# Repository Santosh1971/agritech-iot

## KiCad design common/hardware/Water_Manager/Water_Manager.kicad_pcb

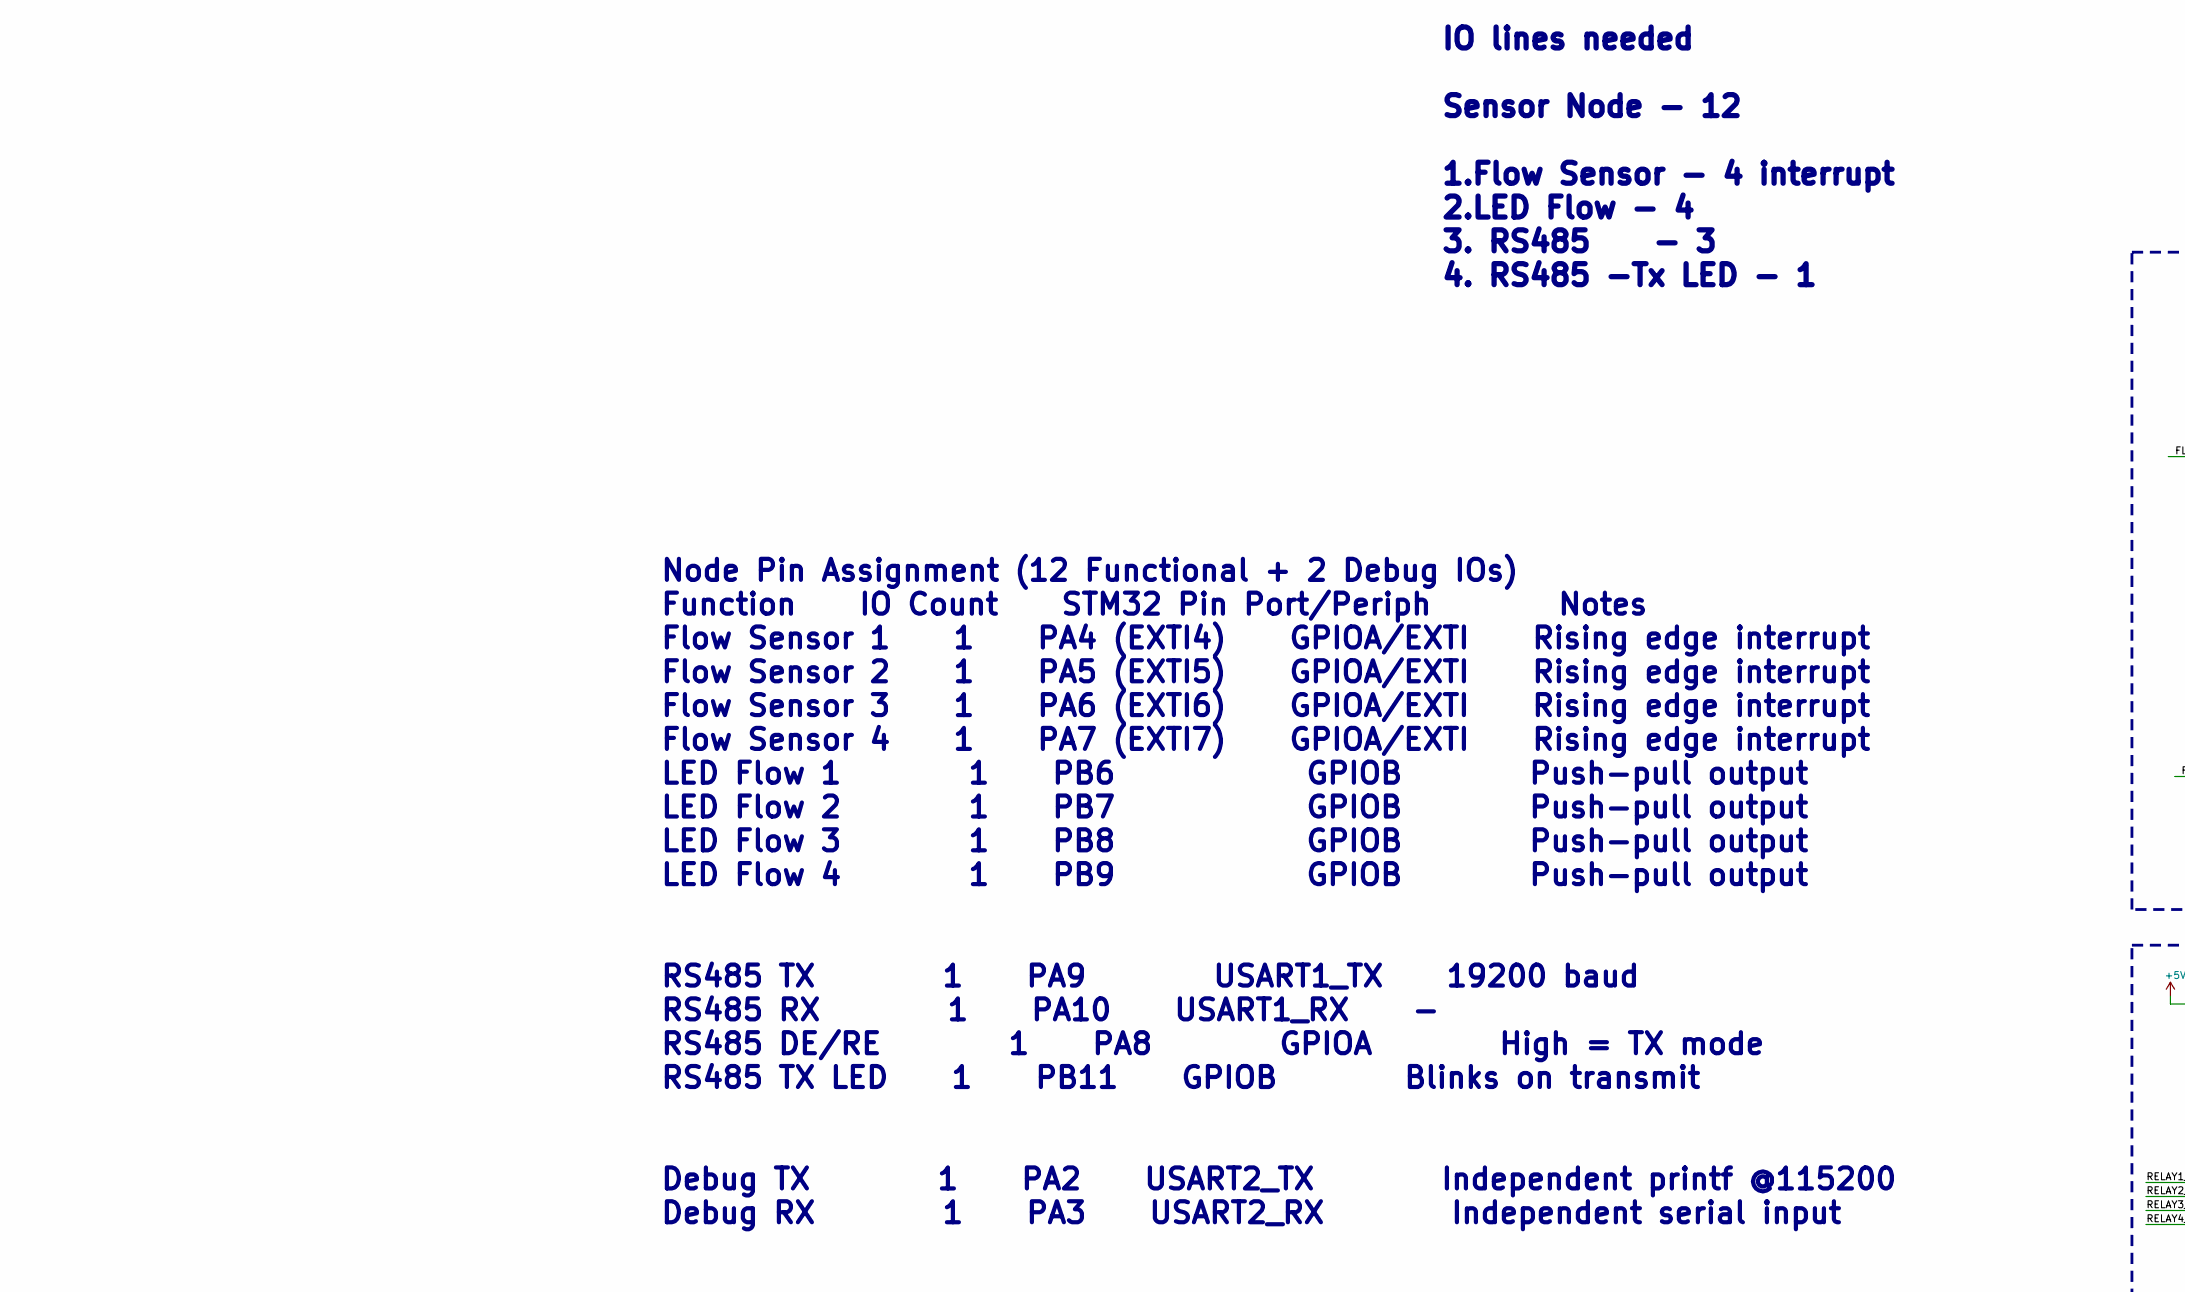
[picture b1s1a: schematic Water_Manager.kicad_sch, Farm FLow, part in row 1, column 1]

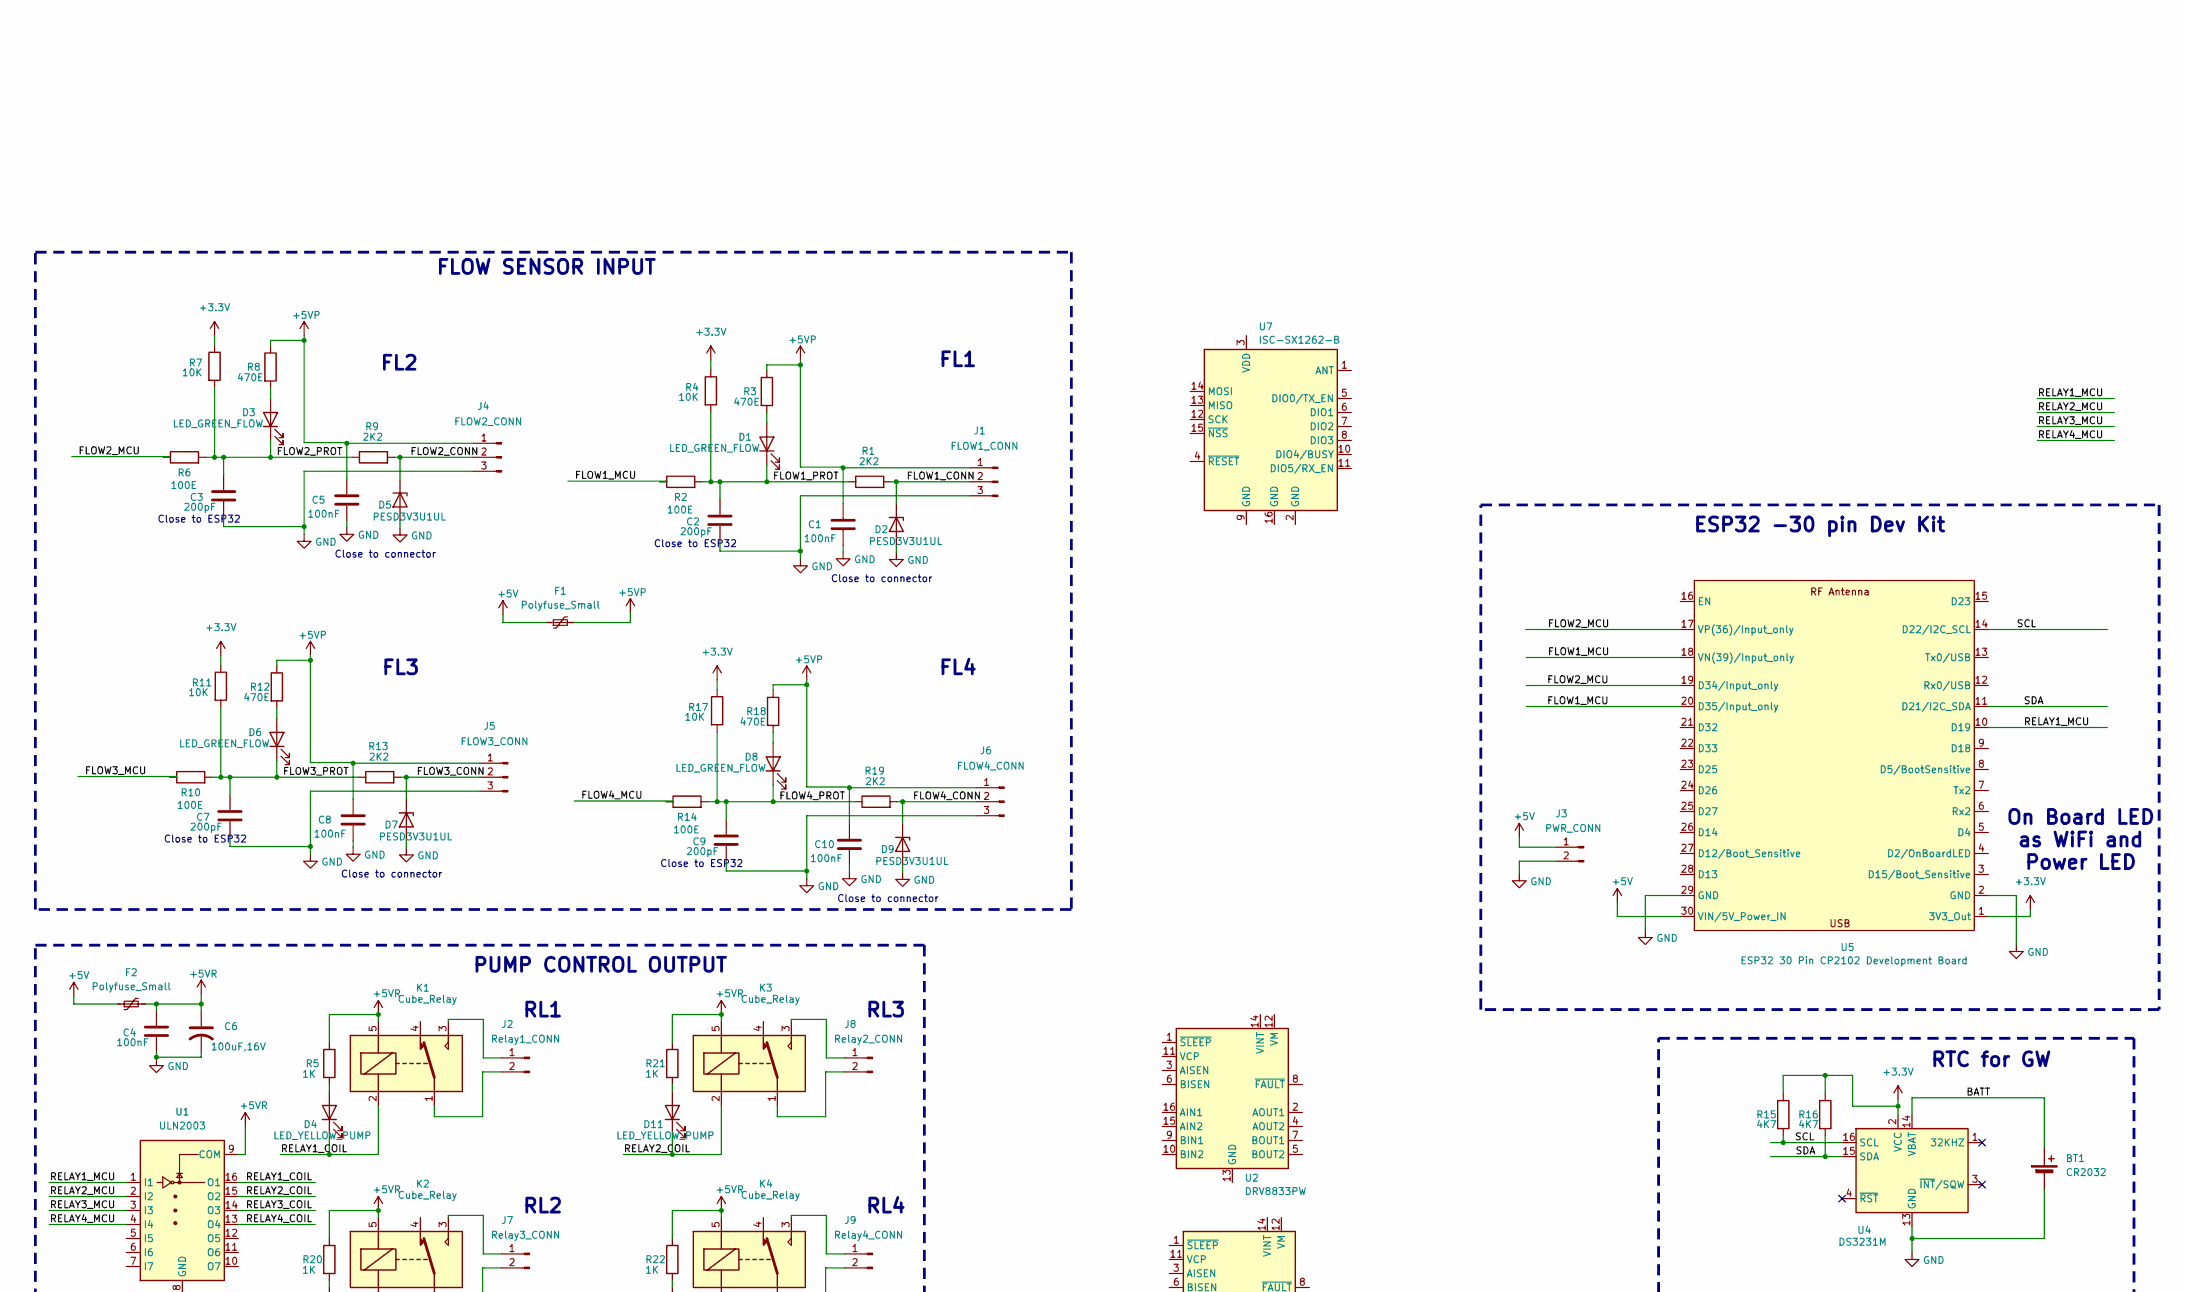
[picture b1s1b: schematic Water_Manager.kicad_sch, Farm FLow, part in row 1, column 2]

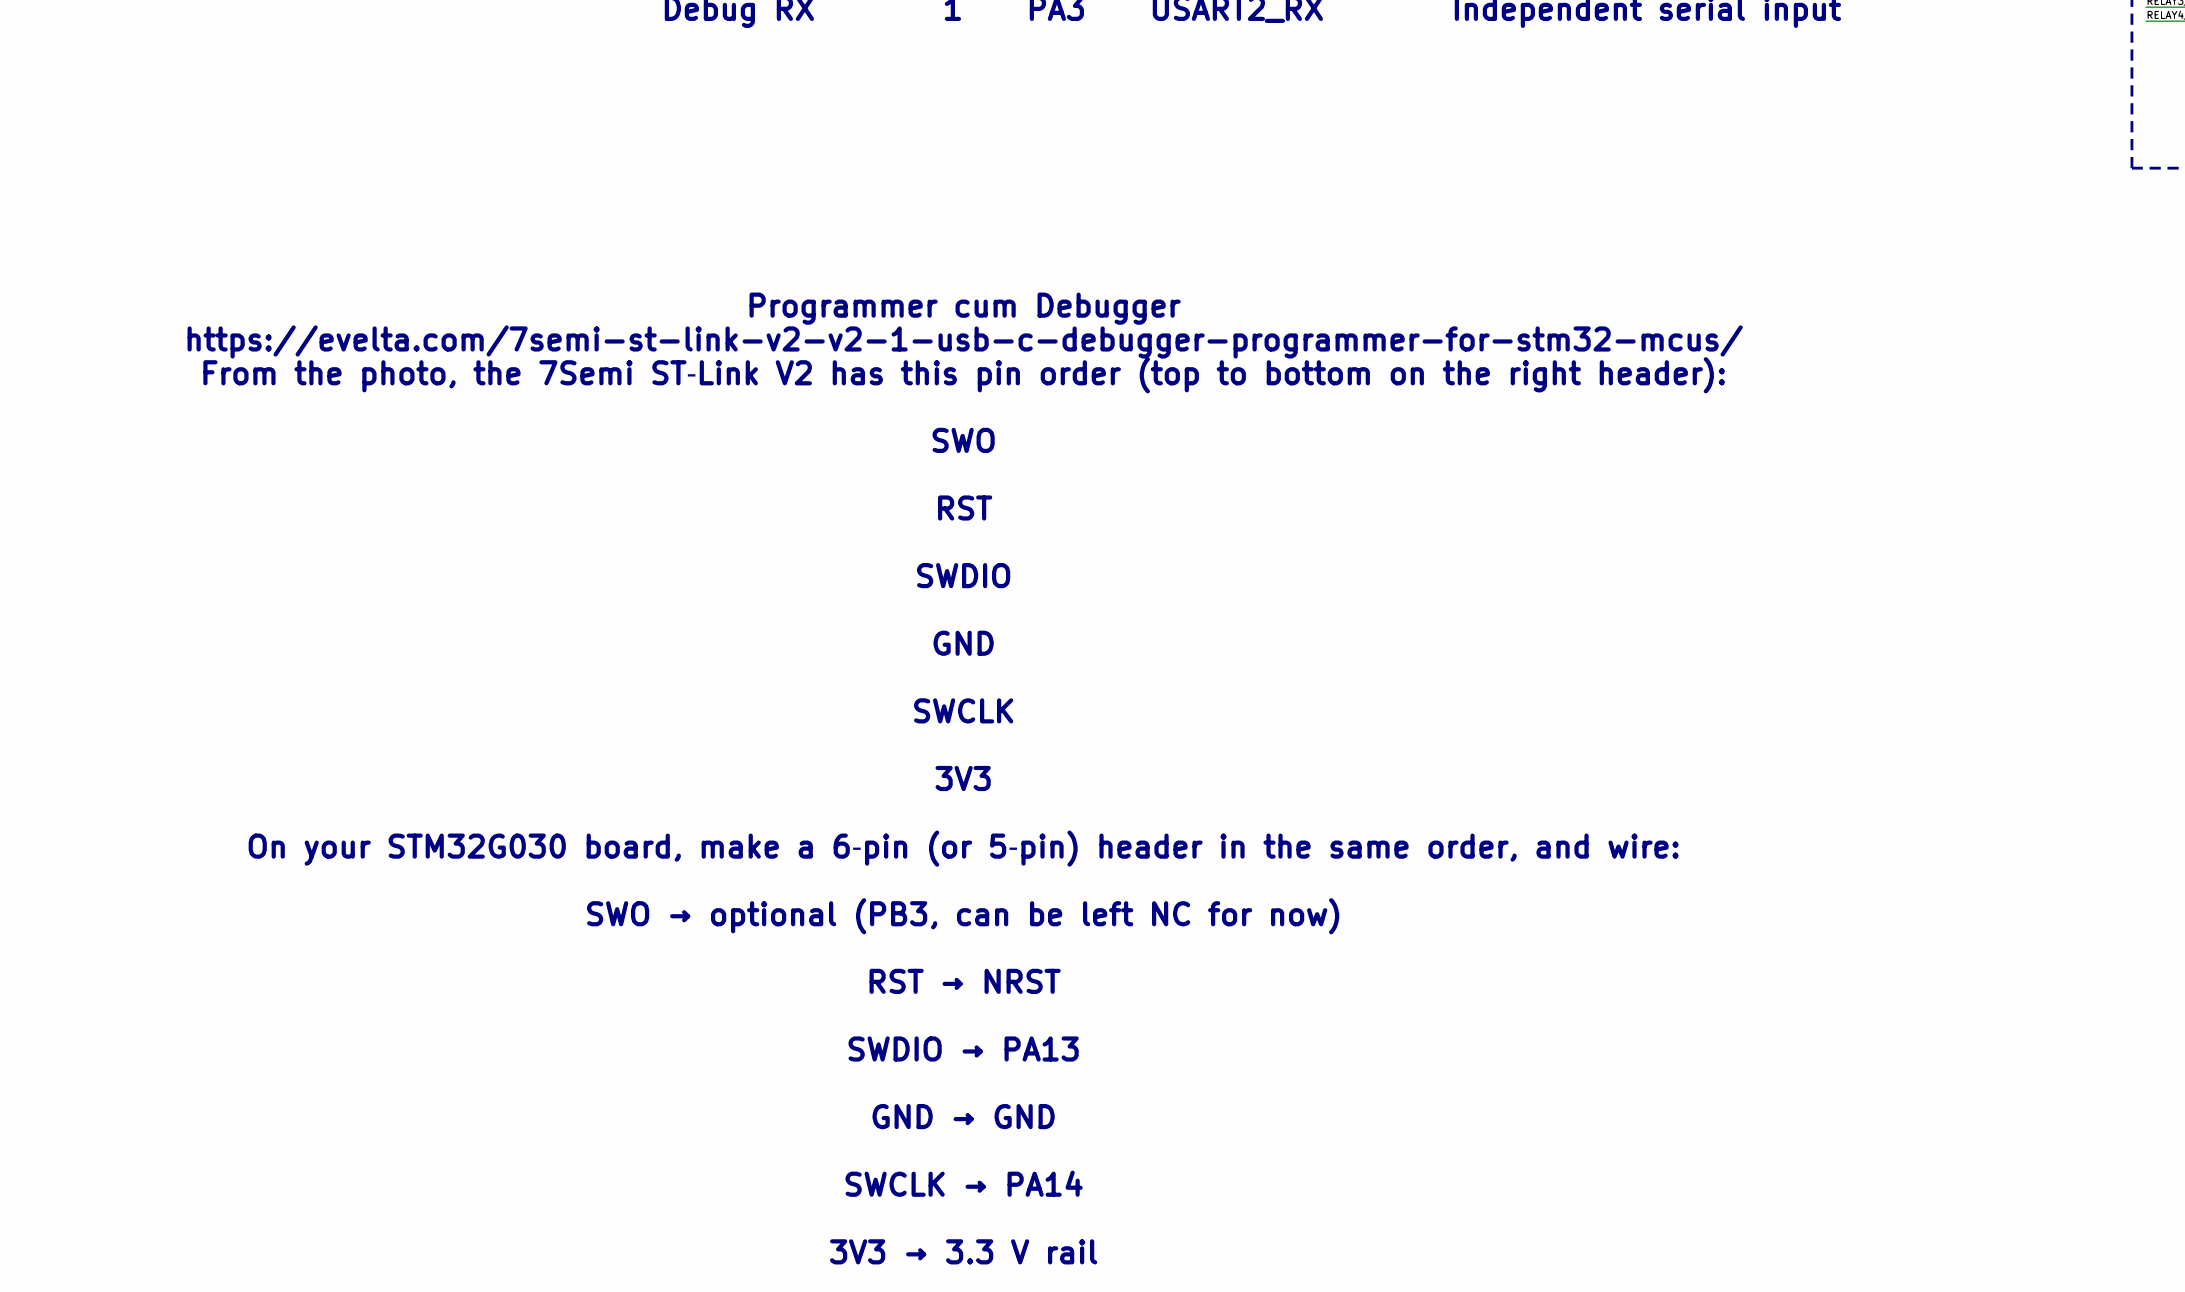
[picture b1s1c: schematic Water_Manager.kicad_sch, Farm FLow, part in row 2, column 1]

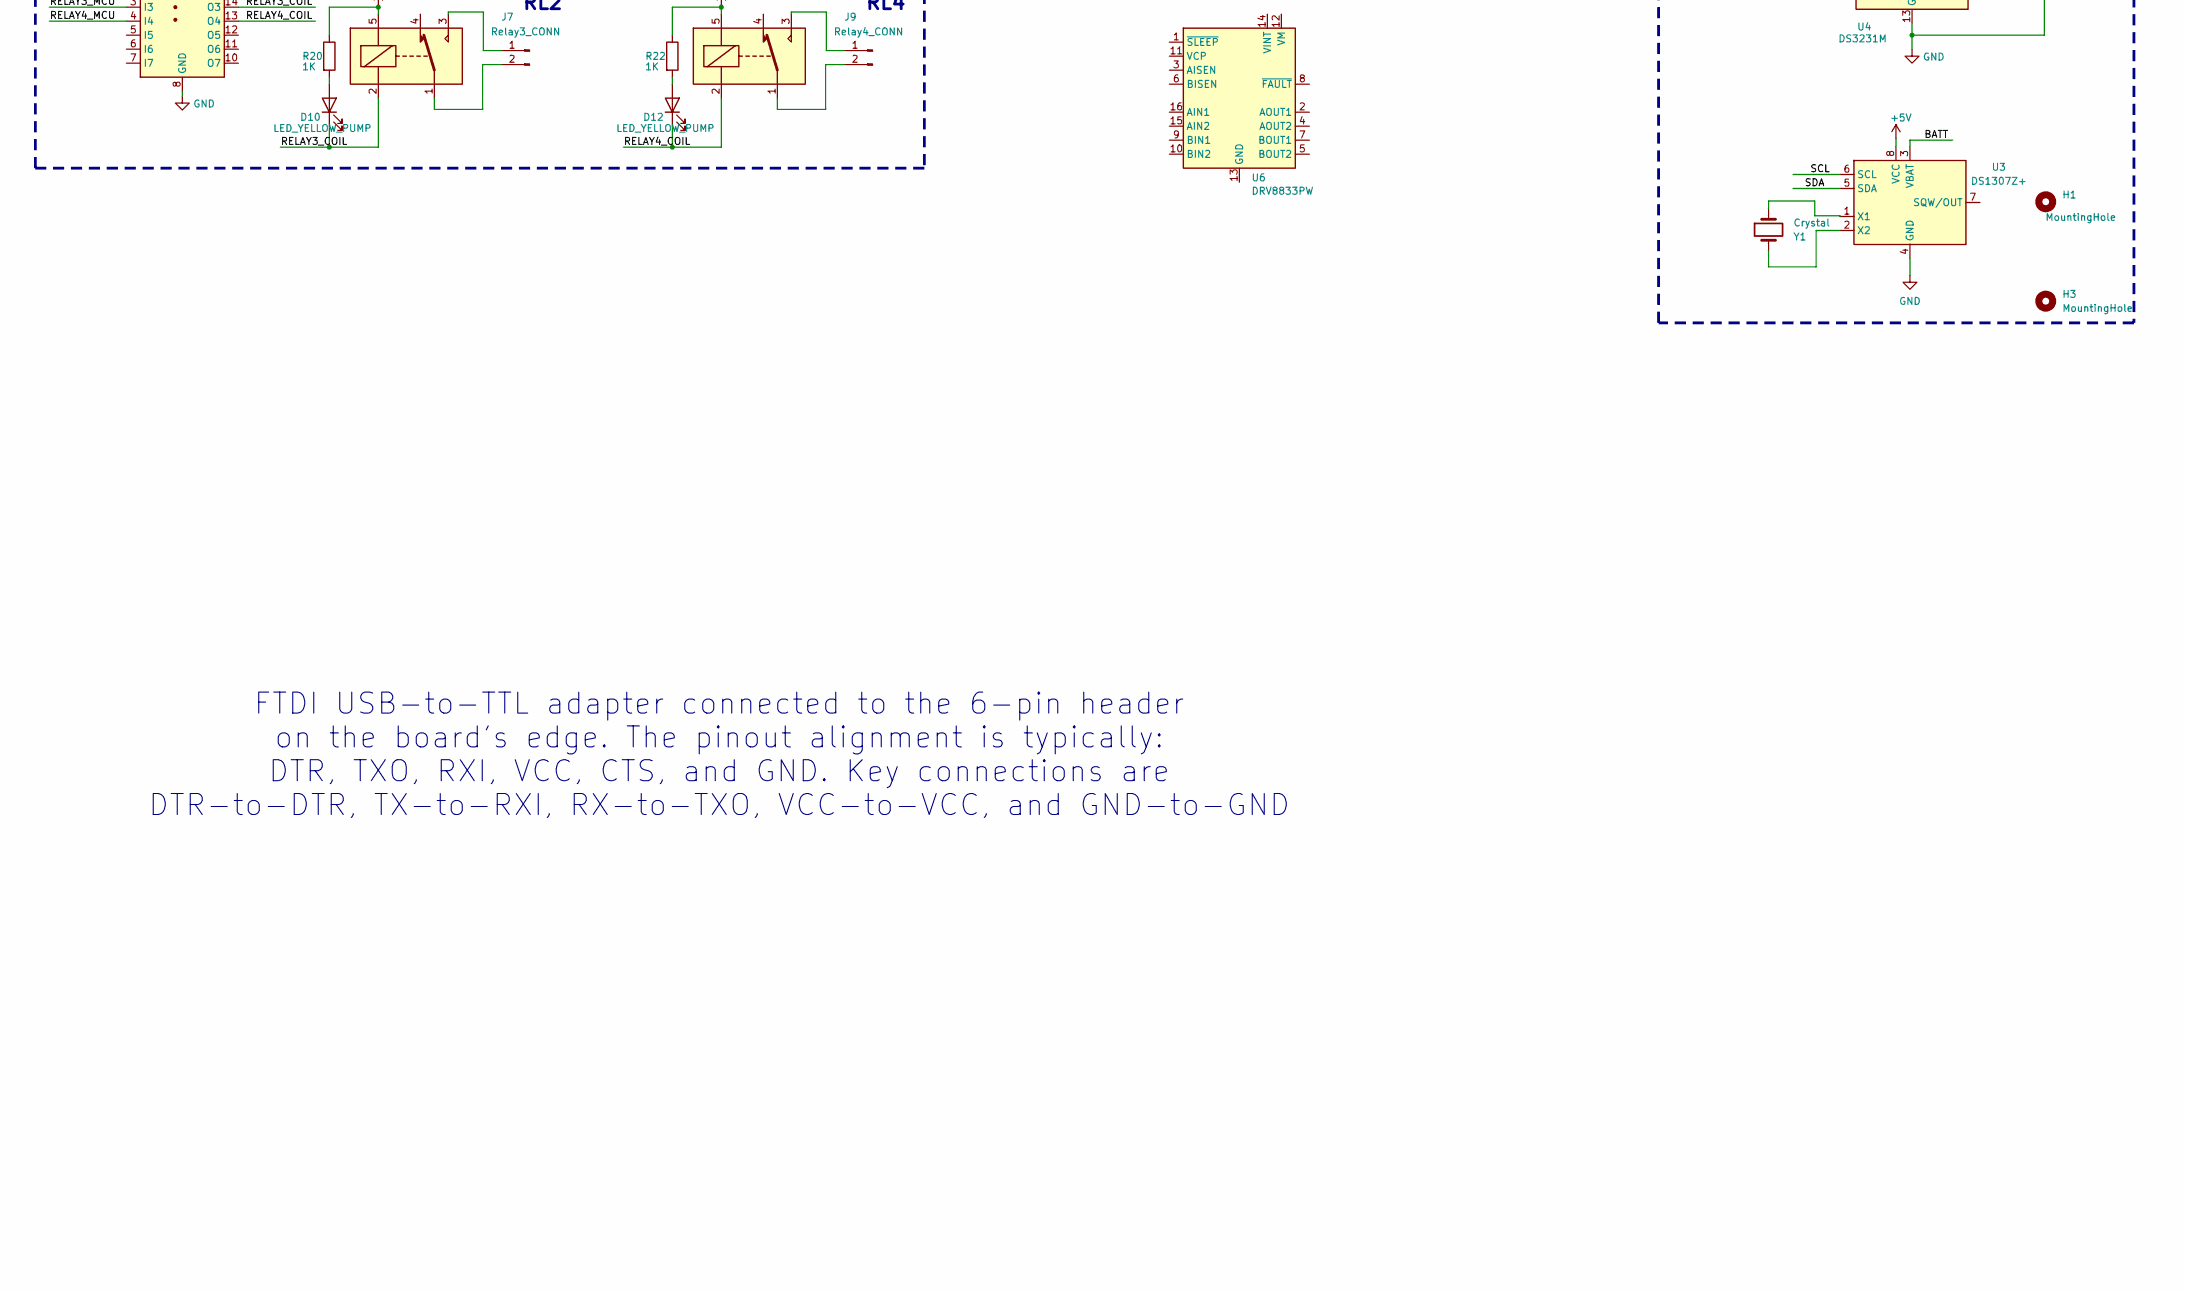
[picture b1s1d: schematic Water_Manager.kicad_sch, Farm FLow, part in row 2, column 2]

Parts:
BT1: CR2032
C1, C4, C5, C8, C10: 100nF; C_0805_2012Metric
C2, C3, C7, C9: 200pF; C_0805_2012Metric
C6: 100uF,16V; C_Radial_D5.0mm_H7.0mm_P2.00mm
D1, D3, D6, D8: LED_GREEN_FLOW; LED_0603_1608Metric
D2, D5, D7, D9: PESD3V3U1UL; D_SOD-882
D4, D10, D11, D12: LED_YELLOW_PUMP; LED_0603_1608Metric
F1, F2: Polyfuse_Small; L_1206_3216Metric
H1, H3: MountingHole; MountingHole_3.2mm_M3
J1: FLOW1_CONN; JST_EH_B3B-EH-A_1x03_P2.50mm_Vertical
J2: Relay1_CONN; JST_EH_B2B-EH-A_1x02_P2.50mm_Vertical
J3: PWR_CONN
J4: FLOW2_CONN; JST_EH_B3B-EH-A_1x03_P2.50mm_Vertical
J5: FLOW3_CONN; JST_EH_B3B-EH-A_1x03_P2.50mm_Vertical
J6: FLOW4_CONN; JST_EH_B3B-EH-A_1x03_P2.50mm_Vertical
J7: Relay3_CONN; JST_EH_B2B-EH-A_1x02_P2.50mm_Vertical
J8: Relay2_CONN; JST_EH_B2B-EH-A_1x02_P2.50mm_Vertical
J9: Relay4_CONN; JST_EH_B2B-EH-A_1x02_P2.50mm_Vertical
K1, K2, K3, K4: Cube_Relay; Relay_SPDT_SANYOU_SRD_Series_Form_C
R1, R9, R13, R19: 2K2; R_0805_2012Metric
R2, R6, R10, R14: 100E; R_0805_2012Metric
R3, R8, R12, R18: 470E; R_0805_2012Metric
R4, R7, R11, R17: 10K; R_0805_2012Metric
R5, R20, R21, R22: 1K; R_0805_2012Metric
R15, R16: 4K7; R_0805_2012Metric
U1: ULN2003; SOIC-16W_5.3x10.2mm_P1.27mm
U2, U6: DRV8833PW; TSSOP-16_4.4x5mm_P0.65mm
U3: DS1307Z+; SOIC-8_3.9x4.9mm_P1.27mm
U4: DS3231M; SOIC-16W_7.5x10.3mm_P1.27mm
U5: ESP32 30 Pin CP2102 Development Board; ESP32-C3-DevKitM-1
U7: ISC-SX1262-B; ISC-LoRa
Y1: Crystal; Crystal_AT310_D3.0mm_L10.0mm_Horizontal

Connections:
+3.3V: R4.1, R7.1, R11.1, R15.1, R16.1, R17.1, U4.2 (VCC), U5.1 (3V3_Out)
+5V: F1.1, F2.1, J3.1, U3.8 (VCC), U5.30 (VIN/5V_Power_IN); also elsewhere on the board
+5VP: C1.1, C5.1, C8.1, C10.1, F1.2, J1.1, J4.1, J5.1, J6.1, R3.1, R8.1, R12.1, R18.1
+5VR: C4.1, C6.1, F2.2, K1.5, K2.5, K3.5, K4.5, R5.1, R20.1, R21.1, R22.1, U1.9 (COM)
/BATT: BT1.1 (+), U3.3 (VBAT), U4.14 (VBAT)
/FLOW1_CONN: D2.1 (K), J1.2, R1.2
/FLOW1_MCU: R2.1, U5.18 (VN(39)/Input_only), U5.20 (D35/Input_only)
/FLOW1_PROT: C2.1, D1.1 (K), R1.1, R2.2, R4.2
/FLOW2_CONN: D5.1 (K), J4.2, R9.2
/FLOW2_MCU: R6.1, U5.17 (VP(36)/Input_only), U5.19 (D34/Input_only)
/FLOW2_PROT: C3.1, D3.1 (K), R6.2, R7.2, R9.1
/FLOW3_CONN: D7.1 (K), J5.2, R13.2
/FLOW3_MCU: R10.1
/FLOW3_PROT: C7.1, D6.1 (K), R10.2, R11.2, R13.1
/FLOW4_CONN: D9.1 (K), J6.2, R19.2
/FLOW4_MCU: R14.1
/FLOW4_PROT: C9.1, D8.1 (K), R14.2, R17.2, R19.1
/RELAY1_COIL: D4.1 (K), K1.2, U1.16 (O1)
/RELAY1_MCU: U1.1 (I1), U5.10 (D19)
/RELAY2_COIL: D11.1 (K), K3.2, U1.15 (O2)
/RELAY2_MCU: U1.2 (I2)
/RELAY3_COIL: D10.1 (K), K2.2, U1.14 (O3)
/RELAY3_MCU: U1.3 (I3)
/RELAY4_COIL: D12.1 (K), K4.2, U1.13 (O4)
/RELAY4_MCU: U1.4 (I4)
/SCL: R15.2, U3.6 (SCL), U4.16 (SCL), U5.14 (D22/I2C_SCL)
/SDA: R16.2, U3.5 (SDA), U4.15 (SDA), U5.11 (D21/I2C_SDA)
GND: BT1.2 (-), C1.2, C2.2, C3.2, C4.2, C5.2, C6.2, C7.2, C8.2, C9.2, C10.2, D2.2 (A), D5.2 (A), D7.2 (A), D9.2 (A), J1.3, J3.2, J4.3, J5.3, J6.3, U1.8 (GND), U3.4 (GND), U4.5 (GND), U4.6 (GND), U4.7 (GND), U4.8 (GND), U4.9 (GND), U4.10 (GND), U4.11 (GND), U4.12 (GND), U4.13 (GND), U5.2 (GND), U5.29 (GND); also elsewhere on the board
unnamed: D1.2 (A), R3.2
unnamed: D3.2 (A), R8.2
unnamed: D4.2 (A), R5.2
unnamed: D6.2 (A), R12.2
unnamed: D8.2 (A), R18.2
unnamed: D10.2 (A), R20.2
unnamed: D11.2 (A), R21.2
unnamed: D12.2 (A), R22.2
unnamed: J2.1, K1.3
unnamed: J2.2, K1.1
unnamed: J7.1, K2.3
unnamed: J7.2, K2.1
unnamed: J8.1, K3.3
unnamed: J8.2, K3.1
unnamed: J9.1, K4.3
unnamed: J9.2, K4.1
unnamed: U3.1 (X1), Y1.1
unnamed: U3.2 (X2), Y1.2
unnamed: U7.2 (GND), U7.9 (GND), U7.16 (GND)

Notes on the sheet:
Close to connector
Close to ESP32
FL4
Programmer cum Debugger https://evelta.com/7semi-st-link-v2-v2-1-usb-c-debugger-programmer-for-stm32-mcus/ From the photo, the 7Semi ST‑Link V2 has this pin order (top to bottom on the right header): SWO RST SWDIO GND SWCLK 3V3 On your STM32G030 board, make a 6‑pin (or 5‑pin) header in the same ord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
RL3
IO lines needed Sensor Node - 12 1.Flow Sensor - 4 interrupt 2.LED Flow - 4 3. RS485 - 3 4. RS485 -Tx LED - 1
RTC for GW
RL4
On Board LED as WiFi and Power LED
Node Pin Assignment (12 Functional + 2 Debug IOs) Function IO Count STM32 Pin Port/Periph Notes Flow Sensor 1 1 PA4 (EXTI4) GPIOA/EXTI Rising edge interrupt Flow Sensor 2 1 PA5 (EXTI5) GPIOA/EXTI Rising edge interrupt Flow Sensor 3 1 PA6 (EXTI6) GPIOA/EXTI Rising edge interrupt Flow Sensor 4 1 PA7 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
FTDI USB-to-TTL adapter connected to the 6-pin header on the board's edge. The pinout alignment is typically: DTR, TXO, RXI, VCC, CTS, and GND. Key connections are DTR-to-DTR, TX-to-RXI, RX-to-TXO, VCC-to-VCC, and GND-to-GND
PUMP CONTROL OUTPUT
ESP32 -30 pin Dev Kit
RL1
FL3
RL2
FL1
FLOW SENSOR INPUT
FL2

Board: 2 copper layers, 76 parts (45 on the bottom side), 42 nets, no tracks yet.

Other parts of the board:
.: MountingHole; MountingHole_3.2mm_M3
J3#2: PWR_CONN; PinHeader_1x02_P2.00mm_Vertical
J3#3, J3#4, J3#5, J3#6: PWR_CONN; JST_EH_B2B-EH-A_1x02_P2.50mm_Vertical

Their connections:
+5V: J3#2.1, J3#4.1; also elsewhere on the board
GND: J3#2.2, J3#4.2; also elsewhere on the board

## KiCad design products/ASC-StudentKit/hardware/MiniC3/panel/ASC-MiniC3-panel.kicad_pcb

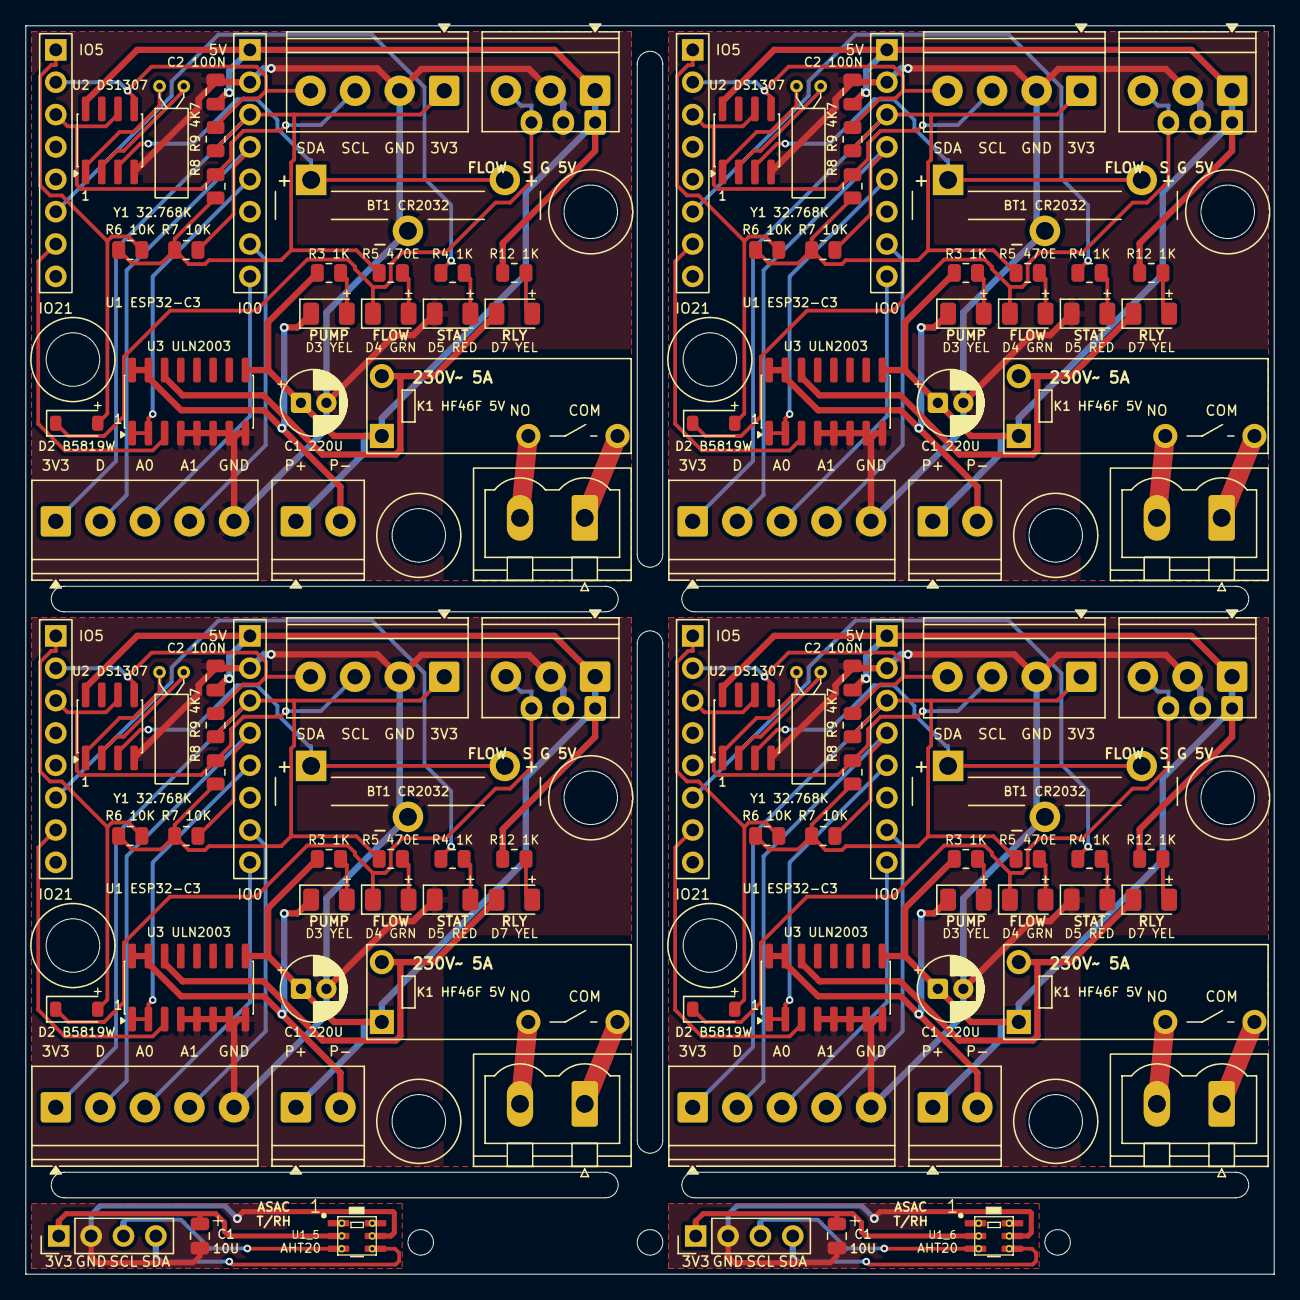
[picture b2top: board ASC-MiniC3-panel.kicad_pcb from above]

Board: 2 copper layers, 98.0 x 98.0 mm, 122 parts (0 on the bottom side), 104 nets.

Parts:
BT1_1, BT1_2, BT1_3, BT1_4: CR2032 tabbed; Battery_CR2032_Vertical_3pin
C1_1, C1_2, C1_3, C1_4: 220u 10V; CP_Radial_D5.0mm_P2.00mm
C1_5, C1_6: 10u; C_0805_2012Metric
C2_1, C2_2, C2_3, C2_4: 100n; C_0805_2012Metric
D2_1, D2_2, D2_3, D2_4: B5819W; D_SOD-123
D3_1, D3_2, D3_3, D3_4: PUMP yellow; LED_1206_3216Metric
D4_1, D4_2, D4_3, D4_4: FLOW yellow-green; LED_1206_3216Metric
D5_1, D5_2, D5_3, D5_4: STATUS red; LED_1206_3216Metric
D7_1, D7_2, D7_3, D7_4: RELAY yellow; LED_1206_3216Metric
H1_1, H1_2, H1_3, H1_4, H2_1, H2_2, H2_3, H2_4, H3_1, H3_2, H3_3, H3_4: SNAP 4.2; Snap_Standoff_4.2mm
J1_1, J1_2, J1_3, J1_4: PUMP; TerminalBlock_Phoenix_PT-1,5-2-3.5-H_1x02_P3.50mm_Horizontal
J1_5, J1_6: CABLE; PinHeader_1x04_P2.54mm_Vertical
J3_1, J3_2, J3_3, J3_4: AUX; TerminalBlock_Phoenix_PT-1,5-5-3.5-H_1x05_P3.50mm_Horizontal
J4_1, J4_2, J4_3, J4_4: FLOW (XH or 3.5 mm); Flow_XH3_or_PT-1,5-3-3.5mm
J5_1, J5_2, J5_3, J5_4: I2C; TerminalBlock_Phoenix_PT-1,5-4-3.5-H_1x04_P3.50mm_Horizontal
J6_1, J6_2, J6_3, J6_4: RELAY 230V (MSTBVA); PhoenixContact_MSTBVA_2,5_2-G-5,08_1x02_P5.08mm_Vertical
K1_1, K1_2, K1_3, K1_4: HF46F/005-HS1; Relay_SPST_Hongfa_HF46F
R3_1, R3_2, R3_3, R3_4, R4_1, R4_2, R4_3, R4_4, R12_1, R12_2, R12_3, R12_4: 1k; R_0805_2012Metric
R5_1, R5_2, R5_3, R5_4: 470; R_0805_2012Metric
R6_1, R6_2, R6_3, R6_4, R7_1, R7_2, R7_3, R7_4: 10k; R_0805_2012Metric
R8_1, R8_2, R8_3, R8_4, R9_1, R9_2, R9_3, R9_4: 4.7k; R_0805_2012Metric
U1_1, U1_2, U1_3, U1_4: ESP32-C3 Super Mini; ESP32-C3_SuperMini_Socket
U1_5, U1_6: AHT20; Aosong_AHT20_DFN-6_3x3mm
U2_1, U2_2, U2_3, U2_4: DS1307Z+; SOIC-8_3.9x4.9mm_P1.27mm
U3_1, U3_2, U3_3, U3_4: ULN2003A; SOIC-16_3.9x9.9mm_P1.27mm
Y1_1, Y1_2, Y1_3, Y1_4: 32.768k 12.5pF; Crystal_C26-LF_D2.1mm_L6.5mm_Horizontal

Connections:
B1/+3V3: J3_1.1, J5_1.1, R5_1.1, R6_1.1, R7_1.1, R8_1.1, R9_1.1, U1_1.11
B1/+5V: C1_1.1, C2_1.1, J1_1.1, J4_1.1, K1_1.1, R3_1.1, R12_1.1, U1_1.9, U2_1.8, U3_1.9
B1/AUX_A0: J3_1.3, U1_1.16
B1/AUX_A1: J3_1.4, U1_1.15
B1/AUX_D: J3_1.2, R7_1.2, U1_1.12
B1/FLOW: D2_1.2, R6_1.2, U1_1.1
B1/FLOW_EXT: D2_1.1, D4_1.1, J4_1.3
B1/GND: BT1_1.2, C1_1.2, C2_1.2, D5_1.1, J3_1.5, J4_1.2, J5_1.2, U1_1.10, U2_1.4, U3_1.4, U3_1.5, U3_1.6, U3_1.7, U3_1.8
B1/LED_FLOW_A: D4_1.2, R5_1.2
B1/LED_PUMP_A: D3_1.2, R3_1.2
B1/LED_RLY_A: D7_1.2, R12_1.2
B1/LED_STATUS: R4_1.1, U1_1.6
B1/LED_STATUS_A: D5_1.2, R4_1.2
B1/PUMP: U1_1.13, U3_1.1, U3_1.2
B1/PUMP_N: D3_1.1, J1_1.2, U3_1.15, U3_1.16
B1/RELAY: U1_1.7, U3_1.3
B1/RELAY_COIL: D7_1.1, K1_1.2, U3_1.14
B1/RELAY_COM: J6_1.1, K1_1.4
B1/RELAY_NO: J6_1.2, K1_1.3
B1/SCL: J5_1.3, R9_1.2, U1_1.3, U2_1.6
B1/SDA: J5_1.4, R8_1.2, U1_1.2, U2_1.5
B1/VBAT: BT1_1.1, U2_1.3
B1/XT1: U2_1.1, Y1_1.1
B1/XT2: U2_1.2, Y1_1.2
B2/+3V3: J3_2.1, J5_2.1, R5_2.1, R6_2.1, R7_2.1, R8_2.1, R9_2.1, U1_2.11
B2/+5V: C1_2.1, C2_2.1, J1_2.1, J4_2.1, K1_2.1, R3_2.1, R12_2.1, U1_2.9, U2_2.8, U3_2.9
B2/AUX_A0: J3_2.3, U1_2.16
B2/AUX_A1: J3_2.4, U1_2.15
B2/AUX_D: J3_2.2, R7_2.2, U1_2.12
B2/FLOW: D2_2.2, R6_2.2, U1_2.1
B2/FLOW_EXT: D2_2.1, D4_2.1, J4_2.3
B2/GND: BT1_2.2, C1_2.2, C2_2.2, D5_2.1, J3_2.5, J4_2.2, J5_2.2, U1_2.10, U2_2.4, U3_2.4, U3_2.5, U3_2.6, U3_2.7, U3_2.8
B2/LED_FLOW_A: D4_2.2, R5_2.2
B2/LED_PUMP_A: D3_2.2, R3_2.2
B2/LED_RLY_A: D7_2.2, R12_2.2
B2/LED_STATUS: R4_2.1, U1_2.6
B2/LED_STATUS_A: D5_2.2, R4_2.2
B2/PUMP: U1_2.13, U3_2.1, U3_2.2
B2/PUMP_N: D3_2.1, J1_2.2, U3_2.15, U3_2.16
B2/RELAY: U1_2.7, U3_2.3
B2/RELAY_COIL: D7_2.1, K1_2.2, U3_2.14
B2/RELAY_COM: J6_2.1, K1_2.4
B2/RELAY_NO: J6_2.2, K1_2.3
B2/SCL: J5_2.3, R9_2.2, U1_2.3, U2_2.6
B2/SDA: J5_2.4, R8_2.2, U1_2.2, U2_2.5
B2/VBAT: BT1_2.1, U2_2.3
B2/XT1: U2_2.1, Y1_2.1
B2/XT2: U2_2.2, Y1_2.2
B3/+3V3: J3_3.1, J5_3.1, R5_3.1, R6_3.1, R7_3.1, R8_3.1, R9_3.1, U1_3.11
B3/+5V: C1_3.1, C2_3.1, J1_3.1, J4_3.1, K1_3.1, R3_3.1, R12_3.1, U1_3.9, U2_3.8, U3_3.9
B3/AUX_A0: J3_3.3, U1_3.16
B3/AUX_A1: J3_3.4, U1_3.15
B3/AUX_D: J3_3.2, R7_3.2, U1_3.12
B3/FLOW: D2_3.2, R6_3.2, U1_3.1
B3/FLOW_EXT: D2_3.1, D4_3.1, J4_3.3
B3/GND: BT1_3.2, C1_3.2, C2_3.2, D5_3.1, J3_3.5, J4_3.2, J5_3.2, U1_3.10, U2_3.4, U3_3.4, U3_3.5, U3_3.6, U3_3.7, U3_3.8
B3/LED_FLOW_A: D4_3.2, R5_3.2
B3/LED_PUMP_A: D3_3.2, R3_3.2
B3/LED_RLY_A: D7_3.2, R12_3.2
B3/LED_STATUS: R4_3.1, U1_3.6
B3/LED_STATUS_A: D5_3.2, R4_3.2
B3/PUMP: U1_3.13, U3_3.1, U3_3.2
B3/PUMP_N: D3_3.1, J1_3.2, U3_3.15, U3_3.16
B3/RELAY: U1_3.7, U3_3.3
B3/RELAY_COIL: D7_3.1, K1_3.2, U3_3.14
B3/RELAY_COM: J6_3.1, K1_3.4
B3/RELAY_NO: J6_3.2, K1_3.3
B3/SCL: J5_3.3, R9_3.2, U1_3.3, U2_3.6
B3/SDA: J5_3.4, R8_3.2, U1_3.2, U2_3.5
B3/VBAT: BT1_3.1, U2_3.3
B3/XT1: U2_3.1, Y1_3.1
B3/XT2: U2_3.2, Y1_3.2
B4/+3V3: J3_4.1, J5_4.1, R5_4.1, R6_4.1, R7_4.1, R8_4.1, R9_4.1, U1_4.11
B4/+5V: C1_4.1, C2_4.1, J1_4.1, J4_4.1, K1_4.1, R3_4.1, R12_4.1, U1_4.9, U2_4.8, U3_4.9
B4/AUX_A0: J3_4.3, U1_4.16
B4/AUX_A1: J3_4.4, U1_4.15
B4/AUX_D: J3_4.2, R7_4.2, U1_4.12
B4/FLOW: D2_4.2, R6_4.2, U1_4.1
B4/FLOW_EXT: D2_4.1, D4_4.1, J4_4.3
B4/GND: BT1_4.2, C1_4.2, C2_4.2, D5_4.1, J3_4.5, J4_4.2, J5_4.2, U1_4.10, U2_4.4, U3_4.4, U3_4.5, U3_4.6, U3_4.7, U3_4.8
B4/LED_FLOW_A: D4_4.2, R5_4.2
B4/LED_PUMP_A: D3_4.2, R3_4.2
B4/LED_RLY_A: D7_4.2, R12_4.2
B4/LED_STATUS: R4_4.1, U1_4.6
B4/LED_STATUS_A: D5_4.2, R4_4.2
B4/PUMP: U1_4.13, U3_4.1, U3_4.2
B4/PUMP_N: D3_4.1, J1_4.2, U3_4.15, U3_4.16
B4/RELAY: U1_4.7, U3_4.3
B4/RELAY_COIL: D7_4.1, K1_4.2, U3_4.14
B4/RELAY_COM: J6_4.1, K1_4.4
B4/RELAY_NO: J6_4.2, K1_4.3
B4/SCL: J5_4.3, R9_4.2, U1_4.3, U2_4.6
B4/SDA: J5_4.4, R8_4.2, U1_4.2, U2_4.5
B4/VBAT: BT1_4.1, U2_4.3
B4/XT1: U2_4.1, Y1_4.1
B4/XT2: U2_4.2, Y1_4.2
B5/+3V3: C1_5.1, J1_5.1, U1_5.2
B5/GND: C1_5.2, J1_5.2, U1_5.5
B5/SCL: J1_5.3, U1_5.3
B5/SDA: J1_5.4, U1_5.4
B6/+3V3: C1_6.1, J1_6.1, U1_6.2
B6/GND: C1_6.2, J1_6.2, U1_6.5
B6/SCL: J1_6.3, U1_6.3
B6/SDA: J1_6.4, U1_6.4
